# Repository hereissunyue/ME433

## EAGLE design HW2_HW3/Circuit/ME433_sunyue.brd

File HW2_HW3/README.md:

ME433 Advanced Mechatronics
---------------------------------
Assignment 2 and 3   

1. <b>.sch</b>, <b>.brd</b> are in the folder [Circuit](https://github.com/hereissunyue/ME433/tree/master/HW2_HW3/Circuit)<br> 
2. <b>gerber</b> files are in the zip file [ME433_sunyue.zip] (https://github.com/hereissunyue/ME433/raw/master/HW2_HW3/ME433_sunyue.zip)

1. Circuit Schematic
---------------------------------

2. Circuit PCB Board
---------------------------------

3. Circuit PCB Board 3D View
---------------------------------

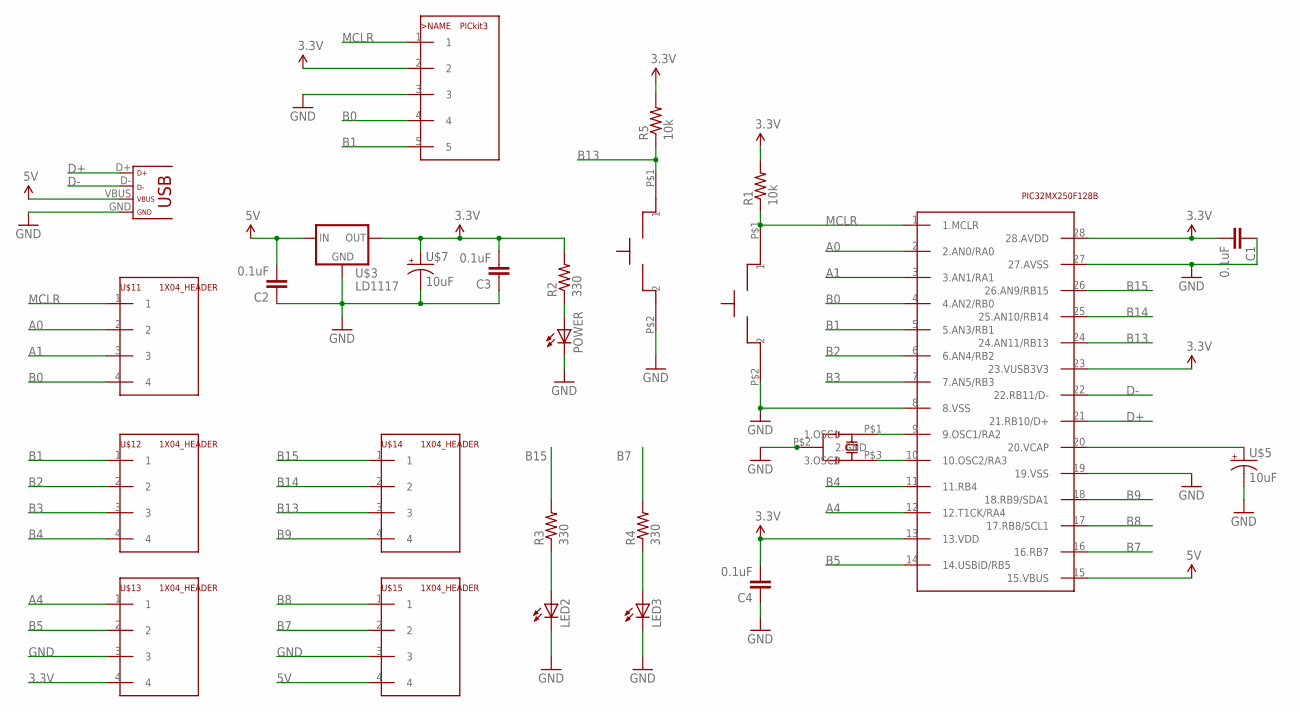
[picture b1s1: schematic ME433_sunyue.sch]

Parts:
>NAME: PICkit3; 1X05
C1, C2, C3, C4: 0.1uF; C025-025X050
LED2, LED3: LED3MM
POWER: LED3MM
R1, R5: 10k; 0207/10
R2, R3, R4: 330; 0207/10
RESET: RESET; BUTTON
U$1: PIC32MX250F128B; DIL28-3
U$2: CRYSTAL
U$3: LD1117; TO220
U$5, U$7: 10uF; CAP_POL_D
U$9: USB; USB-MINIB
U$11, U$12, U$13, U$14, U$15: 1X04_HEADER; 1X04
USER: BUTTON

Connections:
3.3V: >NAME.2, C1.2, C3.2, C4.2, R1.2, R2.2, R5.2, U$1.13 (13.VDD), U$1.23 (23.VUSB3V3), U$1.28 (28.AVDD), U$3.2 (OUT), U$7.1 (+), U$13.4
5V: C2.2, U$1.15 (15.VBUS), U$3.3 (IN), U$9.VBUS, U$15.4
A0: U$1.2 (2.AN0/RA0), U$11.2
A1: U$1.3 (3.AN1/RA1), U$11.3
A4: U$1.12 (12.T1CK/RA4), U$13.1
B0: >NAME.4, U$1.4 (4.AN2/RB0), U$11.4
B1: >NAME.5, U$1.5 (5.AN3/RB1), U$12.1
B2: U$1.6 (6.AN4/RB2), U$12.2
B3: U$1.7 (7.AN5/RB3), U$12.3
B4: U$1.11 (11.RB4), U$12.4
B5: U$1.14 (14.USBID/RB5), U$13.2
B7: R4.2, U$1.16 (16.RB7), U$15.2
B8: U$1.17 (17.RB8/SCL1), U$15.1
B9: U$1.18 (18.RB9/SDA1), U$14.4
B13: R5.1, U$1.24 (24.AN11/RB13), U$14.3, USER.P$1 (1)
B14: U$1.25 (25.AN10/RB14), U$14.2
B15: R3.2, U$1.26 (26.AN9/RB15), U$14.1
D+: U$1.21 (21.RB10/D+), U$9.D+
D-: U$1.22 (22.RB11/D-), U$9.D-
GND: >NAME.3, C1.1, C2.1, C3.1, C4.1, LED2.K (C), LED3.K (C), POWER.K (C), RESET.P$2 (2), U$1.8 (8.VSS), U$1.19 (19.VSS), U$1.27 (27.AVSS), U$2.P$2 (2.GND), U$3.1 (GND), U$5.2 (-), U$7.2 (-), U$9.GND, U$13.3, U$15.3, USER.P$2 (2)
MCLR: >NAME.1, R1.1, RESET.P$1 (1), U$1.1 (1.MCLR), U$11.1
unnamed: U$1.9 (9.OSC1/RA2), U$2.P$1 (1.OSC1)
unnamed: U$1.10 (10.OSC2/RA3), U$2.P$3 (3.OSC2)
unnamed: U$1.20 (20.VCAP), U$5.1 (+)
unnamed: POWER.A, R2.1
unnamed: LED2.A, R3.1
unnamed: LED3.A, R4.1

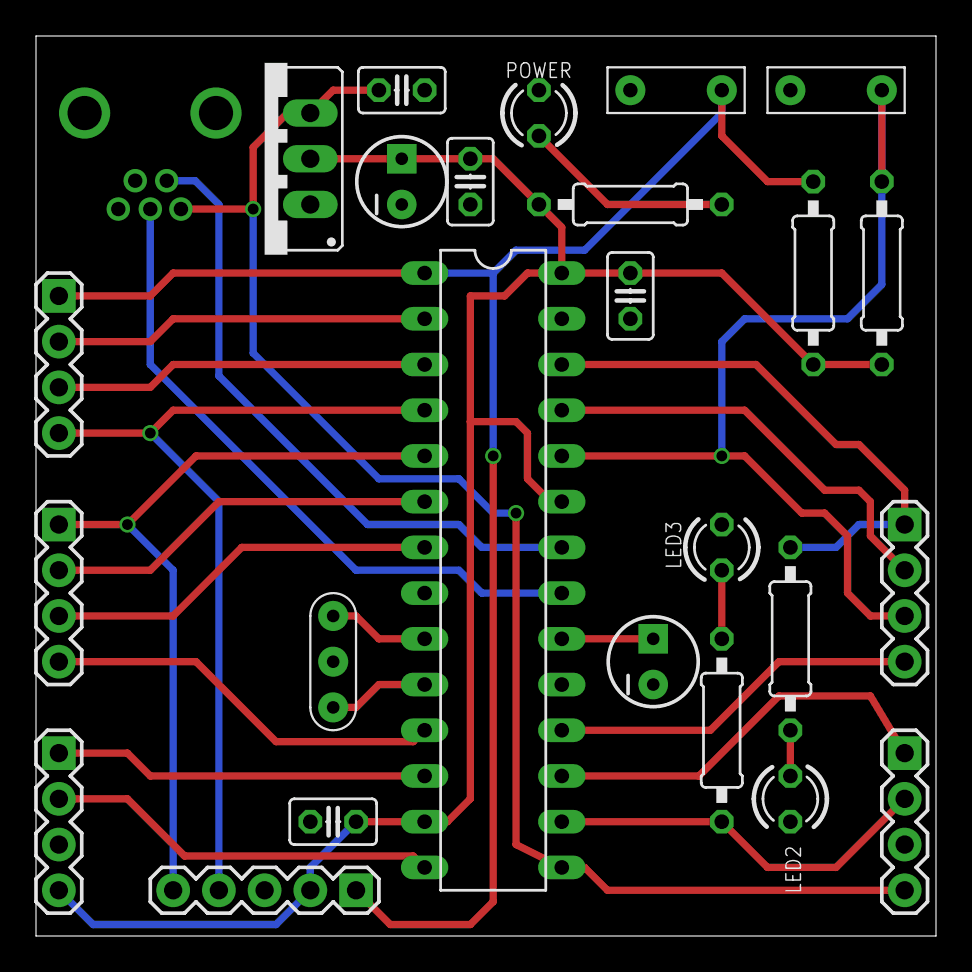
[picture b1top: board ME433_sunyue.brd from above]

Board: 2 copper layers, 50.0 x 50.0 mm, 26 parts (0 on the bottom side), 27 nets.

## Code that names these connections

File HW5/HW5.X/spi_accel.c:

#include "accel.h"
#include <xc.h>
// interface with the LSM303D accelerometer/magnetometer using spi
// Wire GND to GND, VDD to 3.3V, 
// SDO1             -> SDI (labeled SDA),
// SDI1             -> SDO
// SCK1 (B14)       -> SCL
// some digital pin -> CS

#define CS LATBbits.LATB4 // replace x with some digital pin RB4

// send a byte via spi and return the response
unsigned char spi_io(unsigned char o) {
  SPI1BUF = o;
  while(!SPI1STATbits.SPIRBF) { // wait to receive the byte
    ;
  }
  return SPI1BUF;
}


// read data from the accelerometer, given the starting register address.
// return the data in data
void acc_read_register(unsigned char reg, unsigned char data[], unsigned int len) {
  unsigned int i;
  reg |= 0x80; // set the read bit (as per the accelerometer's protocol)
  if(len > 1) 
  {
    reg |= 0x40; // set the address auto increment bit (as per the accelerometer's protocol)
  }
  CS = 0;
  spi_io(reg);
  for(i = 0; i != len; ++i) {
    data[i] = spi_io(0); // read data from spi
  }
  CS = 1;
}


void acc_write_register(unsigned char reg, unsigned char data) {
  CS = 0;               // bring CS low to activate SPI
  spi_io(reg);
  spi_io(data);
  CS = 1;               // complete the command
}


void acc_setup() {
  
  // set up SPI pins configuration
  TRISBbits.TRISB4 = 0;         // 1. set CS to output RA1 and digital if necessary
  ANSELBbits.ANSB14 = 0;        // 2. disable the analog function of RB14
  SDI1Rbits.SDI1R = 0b0001;     // 3. input pin selection SDI1 to be RB5
  ANSELBbits.ANSB2 = 0;         // 4. disable the analog function of RB2
  RPB2Rbits.RPB2R = 0b0011;     // 5. output pin selection SDO1 to be RB2
  CS = 1;

  // Setup the master Master - SPI1
  // we manually control SS as a digital output 
  // since the pic is just starting, we know that spi is off. We rely on defaults here
 
  // setup spi1
  SPI1CON = 0;              // turn off the spi module and reset it
  SPI1BUF;                  // clear the rx buffer by reading from it
  SPI1BRG = 0x3;            // baud rate to 5MHz [SPI1BRG = (40000000/(2*desired))-1]
  SPI1STATbits.SPIROV = 0;  // clear the overflow bit
  SPI1CONbits.CKE = 1;      // data changes when clock goes from active to inactive
                            //    (high to low since CKP is 0)
  SPI1CONbits.MSTEN = 1;    // master operation
  SPI1CONbits.ON = 1;       // turn on spi
 
  // set the accelerometer data rate to 1600 Hz. Do not update until we read values
  acc_write_register(CTRL1, 0xAF); 

  // 50 Hz magnetometer, high resolution, temperature sensor on
  acc_write_register(CTRL5, 0xF0); 

  // enable continuous reading of the magnetometer
  acc_write_register(CTRL7, 0x0); 
  
  // set the accelerometer sensitivity to plus/minus 2g
  acc_write_register(CTRL2, 0x0); 
}

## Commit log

2015-04-06 HW2_HW3
2015-04-07 HW2-HW3
2015-05-22 HW11
2015-05-22 Revert "HW9"
    This reverts commit ec2ef567582812fb300c0658f2addb4b82390822.
2015-05-30 TechCupAndroid
2015-06-06 HW14
2015-06-06 HW10
2015-06-06 HW16
